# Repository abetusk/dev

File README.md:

[Dev Blog](http://mechaelephant.com/dev/)
===

Overview
---

See my [Dev Blog](http://mechaelephant.com/dev/).

Mostly notes for myself in a Blog-esque presentation.

Uses `mkdocs` to generate a list of Blog-like entries.
`orderedlist` is used for the theme.

Compilation
---

```bash
$ mkdocs build
$ mkdocs serve
```

Workflow
---

As a convention, each blog entry is stored in it's own Markdown file, with a timestamp at the end in the form:

```
###### YYYY-MM-DD
```

The compilation workflow is pretty clunky.  To test local, make sure the `base` variable in `mkdocs.yml` is set to `"/"`.
For production deployment, set the `base` variable to `"/dev"`.

Make sure to update a new entry in:

* `wiki/home.md`
* `wiki/Home.textile`
* `wiki/_Sidebar.textile`
* `dev_theme/base.html`
* `mkdocs.yml`

Probably only the `base.html`, `home.md` and `mkdocs.yml` are actually needed.  The others were a hold over from
when I was trying to get things working under GitHub's wiki.

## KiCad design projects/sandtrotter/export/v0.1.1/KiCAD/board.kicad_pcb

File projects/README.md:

Projects
===

###### 2021-01-25

Generative Music
---

### Status

Have a rudimentary song generator at [familiar-synths.js](https://github.com/abetusk/dev/blob/release/notes/src/familiar-synths.js).

The song still isn't quite to my liking as all tunes it generates still sound "same-y".

Gibber (alpha playground) is still having problems with some of the presets, so the preset/instrument library
that can be drawn on is pretty limited.

### todo

* figure out how to make some reasonable generative synths instead of relying on presets
* remove drums at end so they stop
* find instrument sound levels with each other so they play well with each other
* add extra effects (pads, background texture, more complex beats/rythms) to score to help flesh it out
* figure out why the songs sound so stale

| | |
|---|---|
| priority | low |

Sandtrotter
---

### Status

Boards is generated but unordered and the test is unassembled.

### todo

* test out with a nano/arduino with a CR2032 cell to see you can vibrate the motor
* order boards
* create software for it

| | |
|---|---|
| priority | medium |

Live Free, Live Forever
---

### Status

Jacket is assembled but the backing board needs to be paired down.

If there's some way to make the backing easier, this would be ideal.

* Put EVA foam used for floors as a backing plane for the LEDs
* Put EVA foam in both front corners as backing
  - left is for electronics, suitably shoved in there to try and shield it from
    use and offer some strain relief
  - right is for battery
  - might need to elongate the wire from battery to electronics

### todo

* Need to fit to see if the positioning, EVA foam pruning and corner backing
  is reasonable

| | |
|---|---|
| priority | high |

BLDC Driver
---

### Status

Boards are ordered but need to be soldered and tested

* Tested boards
* Big hangup was the 'sense' that needed to either be tied to ground or
  go through a 1ohm resistor
* Let the smoke out of one by connecting it to a large BLDC motor
* Ordered more motors

[src](https://meowcad.com/project?projectId=9ff614c5-18d6-4155-b22e-76b0fd457886)

### todo

* Test with encoder
* Create two motor system with arms to create something interesting
* rev version (?)
  - on board atmega
  - on board encoder (integrated)

| | |
|---|---|
| priority | high |

Seg16
---

### Status

Have a set of 10 boards (put on Tindie) but without a good
method for the diffusors.

The diffusors are laser cut from EVA foam but maybe they
would be better served by 3d printing them.
Seems like kind of a waste of material but who knows.

### todo

* create a clock out of them (or something) as a standalone project

| | |
|---|---|
| priority | medium |

Bloom3d
---

### Status

The 3d printing solution I was pursuing is not going to work.

I think a better method is to have cloth/Tyvek hinges sandwiched in between
laser cut/3d printed/whatever thin strips which then go to a central shaft.

Ordered some tiny stepper motors.
Hopefully they can be driven direct from an Arduino or, in the worst case,
driven by some small transistors.
With luck, I can connect the shaft directly to the platform.

### todo

* get tiny stepper to run (direct off an Arduino)
* construct test rig as proof of concept

| | |
|---|---|
| priority | high |

Frands
---

### Status

Still don't know how to approach this.

Some key points:

* Each layer does not have lights in between them, it's completely
  backlit by the back most panel, diffused from LEDs
* The spacing can be done with foam
* Put it in a frame

### todo

* figure out what the scene should be an implement it

| | |
|---|---|
| priority | low |

BTC Node
---

Create a full node with lightning support.

### Status

None.

### todo

* Either buy a pi + hdd or rent one that has enough space
* stand up node and play around with it

| | |
|---|---|
| priority | high |

Flitterhaus
---

### Status

Software is mostly created, though it needs to be tested a bit.

### todo

* run some outdoor tests on the solar + battery to discover feasibility

| | |
|---|---|
| priority | medium |

Music Similarity
---

### Status

Highly speculative, need to research more.

A modification to `sox` to allow for logarithm frequency spectrogram [here](http://jdesbonnet.blogspot.com/2014/02/sox-spectrogram-log-frequency-axis-and.html) ([gh](https://github.com/jdesbonnet/joe-desbonnet-blog/blob/master/projects/sox-log-spectrogram/spectrogram.c)).

### todo

* find a workflow to create spectrogram, output some type of constellation map
* go back from constellation map to sound to see what gets picked up

| | |
|---|---|
| priority | low |

OK Continuity
---

### Status

Initial investigation is good.
DeepSpeech is faster than real-time.

### todo

* test with usb microphone
* create interface (maybe with visual feedback)
* add some external trigger mechanisms

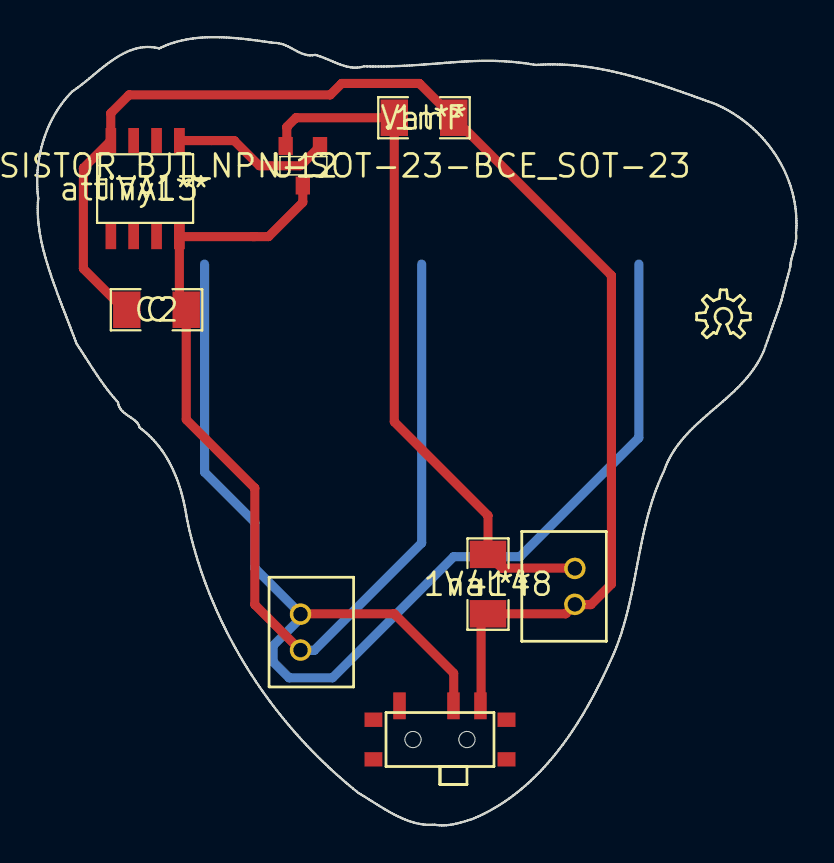
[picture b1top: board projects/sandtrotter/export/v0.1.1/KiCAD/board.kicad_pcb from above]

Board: 5 copper layers, 42.2 x 43.8 mm, 11 parts (0 on the bottom side), 5 nets.

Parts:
1n4148, .1mF: Val**; SM1206
C2: C; SM1206
U12: TRANSISTOR_BJT_NPN-SOT-23-BCE_SOT-23; SOT23
attiny13: VAL**; SO8E
bat: cr2032; BATT2032
ref: val; custom
ref**: val**; SLIDE_SWITCH_SMD
ref**#2: val**; OSHW-LOGO-S
ref**#3, ref**#4: val**; CON_JST_2PIN

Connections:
unnamed: 1n4148.2, .1mF.1, C2.1, attiny13.8, ref**.NC, ref**#4.1
unnamed: C2.2, U12.3, attiny13.4, bat.V-, ref**#3.2
unnamed: 1n4148.1, .1mF.2, U12.2, ref**#4.2
unnamed: U12.1, attiny13.5
unnamed: bat.V1, bat.V2, ref**.COM, ref**#3.1

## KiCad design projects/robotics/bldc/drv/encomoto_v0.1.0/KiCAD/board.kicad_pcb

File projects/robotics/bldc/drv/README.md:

GoPro Driver (L6234)
===

| | |
|---|---|
|  |  | 

BLDC driver based on the L6234 chip.

**Mostly untested**.

Notes
---

* [l6234 datasheet](https://raw.githubusercontent.com/abetusk/manuals/master/datasheets/LD6234.pdf)
* [NearZero](http://skysedge.us/robotics/nearzero/electrical/NearZeroSchematic.pdf)

Tying `SENSE1` and `SENSE2` to ground (or perhaps to a 1 ohm resistor to ground) is necessary,
as I found out.

License
---

CC0

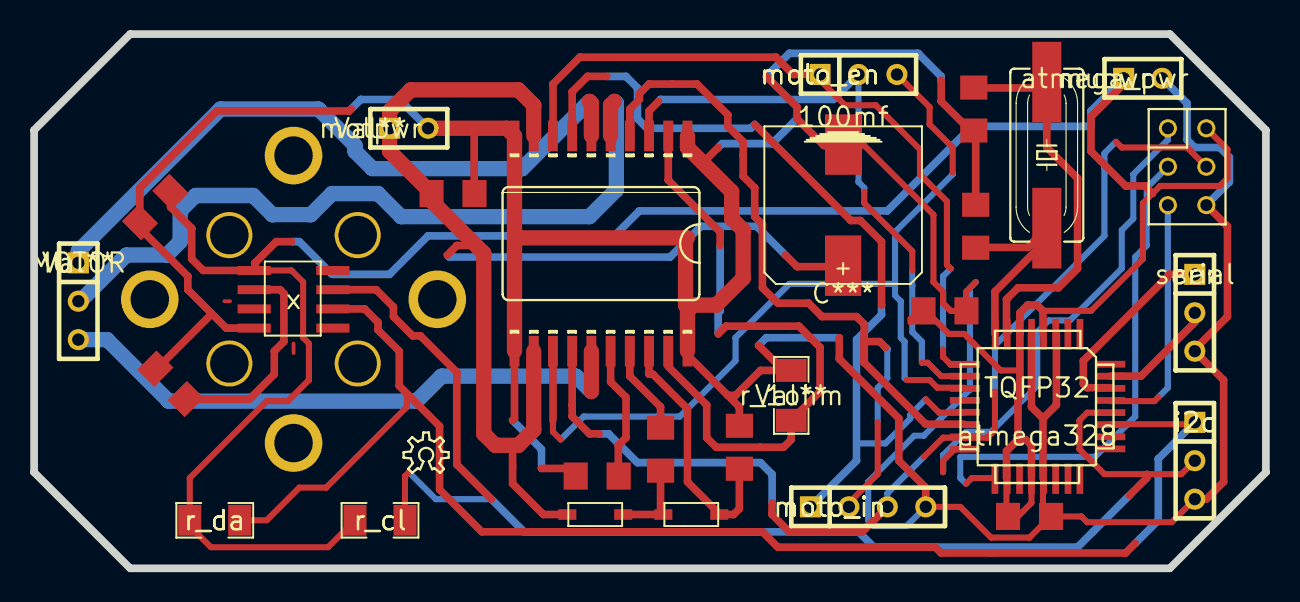
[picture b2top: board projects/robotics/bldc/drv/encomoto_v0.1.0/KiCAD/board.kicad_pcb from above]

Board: 5 copper layers, 81.4 x 35.3 mm, 30 parts (0 on the bottom side), 26 nets.

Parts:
100mf: C***; c_elec_10x10
>NAME: val**; M2X3
>NAME#2: >VALUE; HC49UP
C0e, C12: 100nF; C1206
C1e: 1uF; C1206
C1m: 1uf; C1206
C2: 10nf; C1206
C3: .22uf; C1206
C9: 4.7uF; C1206
C10, C11: 22pF; C1206
D0, D1: 1n4148; SOD-123
MOTOR: Val**; SIL-3
TQFP32: atmega328; TQFP32
U0: l6234; powerSO20
c0: .1uf; C1206
enc: as5600; SOIC-8
i2c: i2c; SIL-3
moto_en: moto_en; SIL-3
moto_in: moto_in; SIL-4
motpwr: Val**; SIL-2
mupwr: atmega_pwr; SIL-2
r_1ohm: Val**; SM1206
r_cl: r_cl; SM1206
r_da: r_da; SM1206
ref**: val**; OSHW-LOGO-S
ser: serial; SIL-3
x: meow_gopro_bot_screw

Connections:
GND: TQFP32.9, TQFP32.14, TQFP32.17, TQFP32.29, TQFP32.31
unnamed: TQFP32.11, TQFP32.12
unnamed: C1e.1, enc.2
unnamed: >NAME.2, C0e.1, C9.1, C12.1, TQFP32.18, enc.1, mupwr.1, r_cl.1, r_da.1
unnamed: enc.7, i2c.2, r_cl.2
unnamed: enc.6, i2c.1, r_da.2
unnamed: U0.2, U0.19, r_1ohm.1
unnamed: >NAME#2.2, C11.1
unnamed: >NAME#2.1, C10.1
unnamed: 100mf.2, >NAME.6, C0e.2, C1e.2, C1m.2, C3.2, C9.2, C10.2, C11.2, C12.2, U0.1, U0.10, U0.11, U0.20, c0.2, enc.4, i2c.3, moto_in.4, motpwr.2, mupwr.2, r_1ohm.2, ser.3
unnamed: U0.8, moto_en.1
unnamed: TQFP32.10, U0.3, moto_en.2
unnamed: U0.13, moto_en.3
unnamed: U0.7, moto_in.1
unnamed: U0.4, moto_in.2
unnamed: >NAME.1, TQFP32.16
unnamed: >NAME.4, TQFP32.15, U0.14, moto_in.3
unnamed: MOTOR.3, U0.15
unnamed: MOTOR.2, U0.5
unnamed: MOTOR.1, U0.6
unnamed: 100mf.1, D0.A, U0.9, U0.12, c0.1, motpwr.1
unnamed: C1m.1, U0.16
unnamed: C2.1, D0.C, D1.A
unnamed: C2.2, U0.17
unnamed: C3.1, D1.C, U0.18
VCC: TQFP32.3, TQFP32.4, TQFP32.13, TQFP32.26

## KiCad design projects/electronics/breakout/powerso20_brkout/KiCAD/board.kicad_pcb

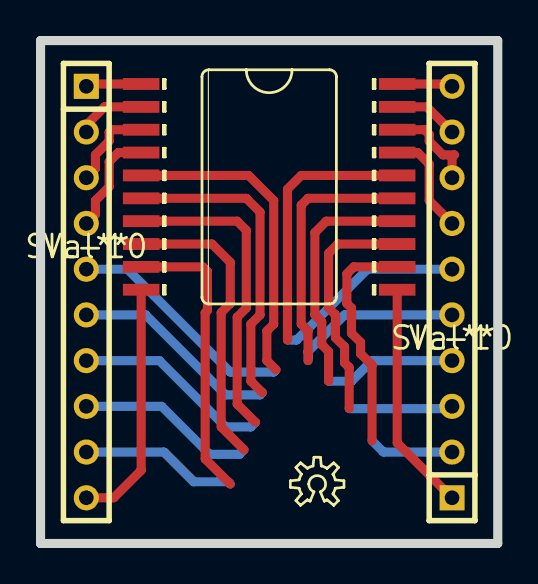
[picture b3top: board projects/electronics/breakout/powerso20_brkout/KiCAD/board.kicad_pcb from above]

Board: 5 copper layers, 25.4 x 27.9 mm, 4 parts (0 on the bottom side), 20 nets.

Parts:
>NAME: >VALUE; powerSO20
SIL-10, SIL-10#2: Val**; SIL-10
ref**: val**; OSHW-LOGO-S

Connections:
unnamed: >NAME.18, SIL-10.8
unnamed: >NAME.19, SIL-10.9
unnamed: >NAME.20, SIL-10.10
unnamed: >NAME.11, SIL-10.1
unnamed: >NAME.12, SIL-10.2
unnamed: >NAME.13, SIL-10.3
unnamed: >NAME.14, SIL-10.4
unnamed: >NAME.15, SIL-10.5
unnamed: >NAME.16, SIL-10.6
unnamed: >NAME.17, SIL-10.7
unnamed: >NAME.6, SIL-10#2.6
unnamed: >NAME.5, SIL-10#2.5
unnamed: >NAME.4, SIL-10#2.4
unnamed: >NAME.3, SIL-10#2.3
unnamed: >NAME.2, SIL-10#2.2
unnamed: >NAME.1, SIL-10#2.1
unnamed: >NAME.7, SIL-10#2.7
unnamed: >NAME.8, SIL-10#2.8
unnamed: >NAME.9, SIL-10#2.9
unnamed: >NAME.10, SIL-10#2.10

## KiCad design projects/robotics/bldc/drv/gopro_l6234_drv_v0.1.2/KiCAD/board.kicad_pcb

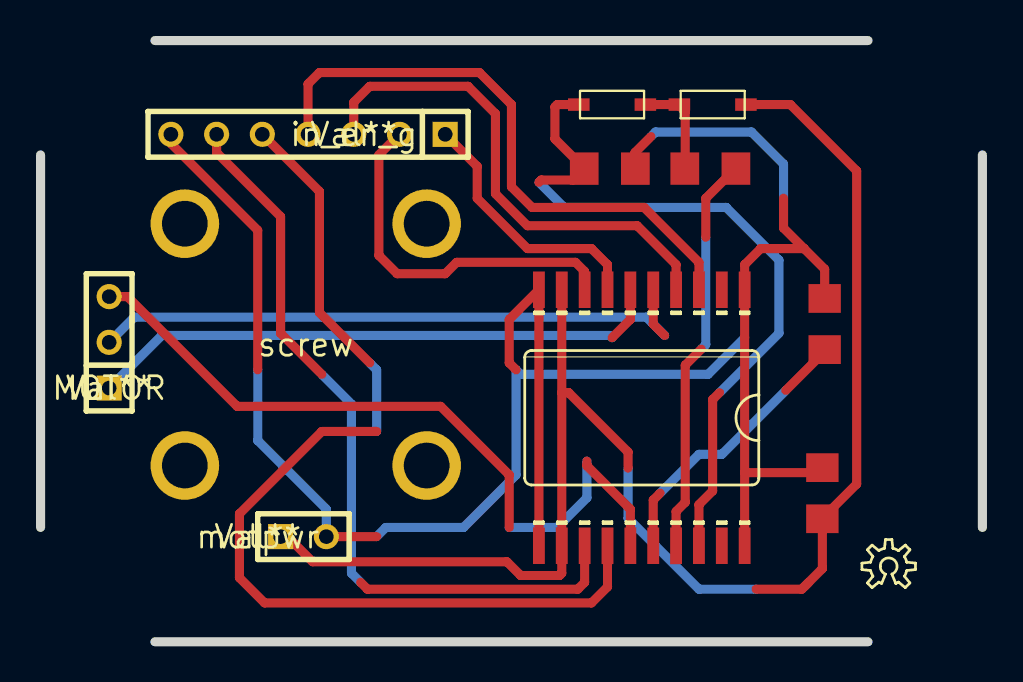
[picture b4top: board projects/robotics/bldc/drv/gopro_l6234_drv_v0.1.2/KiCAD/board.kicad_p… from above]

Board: 5 copper layers, 52.3 x 33.4 mm, 11 parts (0 on the bottom side), 15 nets.

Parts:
C1: 1uf; C1206
C2: 10nf; C1206
C3: .22uf; C1206
D0, D1: 1n4148; SOD-123
MOTOR: Val**; SIL-3
U0: l6234; powerSO20
c0: .1uf; C1206
in_en_g: Val**; SIL-7
motpwr: Val**; SIL-2
ref**: val**; OSHW-LOGO-S

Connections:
unnamed: C1.2, C3.2, U0.1, U0.10, U0.11, U0.20, c0.2, in_en_g.7, motpwr.2
unnamed: D0.A, U0.9, U0.12, c0.1, motpwr.1
unnamed: C1.1, U0.16
unnamed: C2.2, U0.17
unnamed: C3.1, D1.C, U0.18
unnamed: C2.1, D0.C, D1.A
unnamed: U0.3, in_en_g.4
unnamed: U0.7, in_en_g.1
unnamed: MOTOR.3, U0.15
unnamed: MOTOR.2, U0.5
unnamed: MOTOR.1, U0.6
unnamed: U0.8, in_en_g.2
unnamed: U0.4, in_en_g.3
unnamed: U0.14, in_en_g.5
unnamed: U0.13, in_en_g.6

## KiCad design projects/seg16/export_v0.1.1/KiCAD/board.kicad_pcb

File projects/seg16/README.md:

seg16
---

A 16 segment digit (base board) using WS2812B/SK6812 5050 parts.
Size should be about 5.2"x3.9" (132mmx100mm).

Currently this project is **semitested**.

Made with [MeowCAD](https://meowcad.com/project?projectId=4983569d-bf97-47ea-8737-0bbebbcf3797).

| | |
|---|---|
|  |  |

---

###### 2020-10-25

I ordered a set of 10 boards for about $50 from [JLCPCB](https://jlcpcb.com/),
or about $5 per assembled board, with shipping etc.
I used the Gerbers in `export/gerber` along with `BOM` and `CPL` files in the
`wd/jlcpcb` directory.

I haven't actually ordered 30 (which seems to be the max for JLCPCB?) but it comes
to about $112, or about $3.75 per assembled board, with shipping etc. ($86.28 + $25.41 shipping).

###### 2020-11-19

I haven't measured current consumption but [reports rate it](https://www.pjrc.com/how-much-current-do-ws2812-neopixel-leds-really-use/)
at anywhere from 30mA to 50mA (at 5V, so around .15W to .25W).
Each digit is 20 WS2812b, so at full bore that's anywhere from .60A to 1A (or .6W to 5W) per
digit.

If we call it 1A per digit, that means we need about a 20A (100W) power supply for a row of
20 digits.

From some simple experiments, it takes about 2-3 digits before there's a noticeable color degradation
in color.
So, for a single power supply in a row, it's probably wise to distribute power spaced every 2-3 digits.

###### 2020-11-19

The order of the LEDs is given by the following diagram:

License
---

Everything in this directory, unless explicitly denoted otherwise, is
under a CC0 license.

CC0

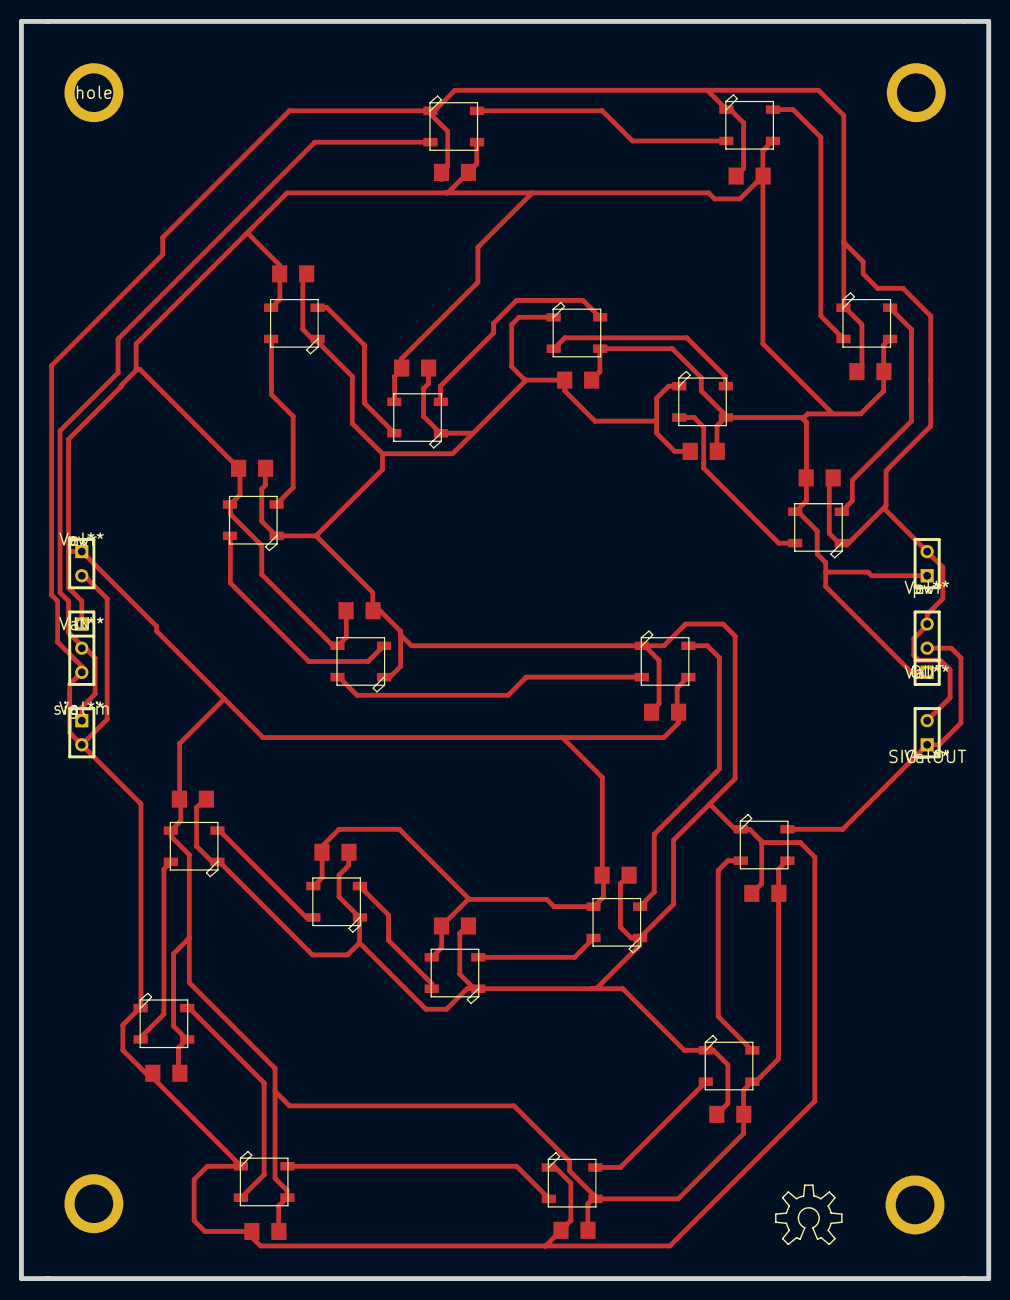
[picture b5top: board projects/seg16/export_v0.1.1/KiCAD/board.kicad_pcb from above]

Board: 5 copper layers, 101.7 x 132.2 mm, 48 parts (0 on the bottom side), 23 nets.

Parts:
C2, C3, C4, C5, C6, C7, C8, C9, C10, C11, C12, C13, C14, C15, C16, C17, C18, C19, C20: C; C1206
IN: Val**; SIL-3
OUT: Val**; SIL-3
SIG-OUT: Val**; SIL-2
U3, U6, U7, U8, U9, U10, U11, U12, U13, U14, U15, U16, U17, U18, U19, U20, U21, U22, U23: WS2812B; meowWS2812B
a0: WS2812B; meowWS2812B
aC0: 100nf; C1206
hole: meow_hole
pwr: Val**; SIL-2
pwr#2: Val**; SIL-2
ref**: val**; OSHW-LOGO-L
sig-in: Val**; SIL-2

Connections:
unnamed: OUT.2, SIG-OUT.1, U8.2-DOUT
unnamed: C2.2, C3.2, C4.2, C5.2, C6.2, C7.2, C8.2, C9.2, C10.2, C11.2, C12.2, C13.2, C14.2, C15.2, C16.2, C17.2, C18.2, C19.2, C20.2, IN.3, OUT.3, SIG-OUT.2, U3.3-GND, U6.3-GND, U7.3-GND, U8.3-GND, U9.3-GND, U10.3-GND, U11.3-GND, U12.3-GND, U13.3-GND, U14.3-GND, U15.3-GND, U16.3-GND, U17.3-GND, U18.3-GND, U19.3-GND, U20.3-GND, U21.3-GND, U22.3-GND, U23.3-GND, a0.3-GND, aC0.2, pwr.2, pwr#2.2, sig-in.2
unnamed: C2.1, C3.1, C4.1, C5.1, C6.1, C7.1, C8.1, C9.1, C10.1, C11.1, C12.1, C13.1, C14.1, C15.1, C16.1, C17.1, C18.1, C19.1, C20.1, IN.1, OUT.1, U3.1-VDD, U6.1-VDD, U7.1-VDD, U8.1-VDD, U9.1-VDD, U10.1-VDD, U11.1-VDD, U12.1-VDD, U13.1-VDD, U14.1-VDD, U15.1-VDD, U16.1-VDD, U17.1-VDD, U18.1-VDD, U19.1-VDD, U20.1-VDD, U21.1-VDD, U22.1-VDD, U23.1-VDD, a0.1-VDD, aC0.1, pwr.1, pwr#2.1
unnamed: U3.4-DIN, a0.2-DOUT
unnamed: IN.2, a0.4-DIN, sig-in.1
unnamed: U3.2-DOUT, U6.4-DIN
unnamed: U6.2-DOUT, U7.4-DIN
unnamed: U7.2-DOUT, U20.4-DIN
unnamed: U9.4-DIN, U10.2-DOUT
unnamed: U10.4-DIN, U11.2-DOUT
unnamed: U11.4-DIN, U12.2-DOUT
unnamed: U12.4-DIN, U13.2-DOUT
unnamed: U15.4-DIN, U18.2-DOUT
unnamed: U14.4-DIN, U15.2-DOUT
unnamed: U16.2-DOUT, U17.4-DIN
unnamed: U17.2-DOUT, U21.4-DIN
unnamed: U18.4-DIN, U19.2-DOUT
unnamed: U19.4-DIN, U20.2-DOUT
unnamed: U21.2-DOUT, U22.4-DIN
unnamed: U22.2-DOUT, U23.4-DIN
unnamed: U14.2-DOUT, U16.4-DIN
unnamed: U13.4-DIN, U23.2-DOUT
unnamed: U8.4-DIN, U9.2-DOUT

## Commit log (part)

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2020-03-18 spindle on fan line
2020-04-02 Non-Violent communication in a nutshell
2020-04-18 spelling
2020-04-18 spelling and todo for instructions
2020-04-18 images
2020-04-18 webui
2020-04-18 webui screens
2020-04-18 svg for compute housing
2020-04-18 housing pic
2020-05-24 graphic in lflf readme
2020-07-19 do away with all that stuff, simple z-axis screw connector
2020-08-10 grbl pinout
2020-08-10 updating notes
2020-08-14 link
2020-10-25 some more documentation
2020-10-25 imperial dimensions
2020-11-25 removed potentially non-free files, added free/libre files
2020-12-21 fighting with markdown
2021-02-18 added license (cc0)
2021-02-18 adding cc0 images
2021-02-18 adding license ingrediant facts
2021-10-26 fighting with newer version of mkdocs
2021-10-26 Bump pillow in /projects/maslowcnc/software/GroundControl-master
    Bumps [pillow](https://github.com/python-pillow/Pillow) from 5.2.0 to 8.3.2.
    - [Release notes](https://github.com/python-pillow/Pillow/releases)
    - [Changelog](https://github.com/python-pillow/Pillow/blob/main/CHANGES.rst)
    - [Commits](https://github.com/python-pillow/Pillow/compare/5.2.0...8.3.2)
    ---
    updated-dependencies:
2022-01-13 Bump pillow in /projects/maslowcnc/software/GroundControl-master
    Bumps [pillow](https://github.com/python-pillow/Pillow) from 5.2.0 to 9.0.0.
    - [Release notes](https://github.com/python-pillow/Pillow/releases)
    - [Changelog](https://github.com/python-pillow/Pillow/blob/main/CHANGES.rst)
    - [Commits](https://github.com/python-pillow/Pillow/compare/5.2.0...9.0.0)
    ---
    updated-dependencies:
2022-03-12 Bump pillow in /projects/maslowcnc/software/GroundControl-master
    Bumps [pillow](https://github.com/python-pillow/Pillow) from 5.2.0 to 9.0.1.
    - [Release notes](https://github.com/python-pillow/Pillow/releases)
    - [Changelog](https://github.com/python-pillow/Pillow/blob/main/CHANGES.rst)
    - [Commits](https://github.com/python-pillow/Pillow/compare/5.2.0...9.0.1)
    ---
    updated-dependencies:
2022-05-29 power polling
2022-09-02 fixing error
    * mu term in product should be back to i, not j
2022-09-08 fixing markdown aggresion for latex matrix expression
2022-11-13 git notes
2022-11-18 formatting
    mathjax (on GH) apparently doesn't like blank lines?
2022-11-18 fixes for latex rendering
    fighting with markdown to get the `*` to render in LaTEX
2022-11-18 0 gh, 1 me
    still fighting with GH vs LaTEX/MathJax.
    It looks like Markdown gets confused when the `*` or `_` symbol is used, especially when it has a partner on the same line. The makeshift solution is to put a `}` directly before the `_` and a space 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
2022-11-22 Bump pillow in /projects/maslowcnc/software/GroundControl-master
    Bumps [pillow](https://github.com/python-pillow/Pillow) from 5.2.0 to 9.3.0.
    - [Release notes](https://github.com/python-pillow/Pillow/releases)
    - [Changelog](https://github.com/python-pillow/Pillow/blob/main/CHANGES.rst)
    - [Commits](https://github.com/python-pillow/Pillow/compare/5.2.0...9.3.0)
    ---
    updated-dependencies:
2022-12-03 fixes
2022-12-17 my continuing fight with GH flavored MD and Latex...
2022-12-30 fighting with latex md
2022-12-30 damn your eyes markdown
2022-12-30 quell jumping sums and roducts
2023-01-03 oof, wrong inequality
    * fixed inequality, added inequality method
    * ...
2023-01-06 mkdocs needs extra '\\' for returns in latex lines?
2023-01-06 latex lines in '$$' multiline instead of single line
2023-01-06 forgot some '\\', fighting with markdown latex
2023-01-06 more fighting with latex markdown, extra '\\'
2023-03-19 incomplete notes
2023-05-22 Bump requests in /projects/maslowcnc/software/GroundControl-master
    Bumps [requests](https://github.com/psf/requests) from 2.13.0 to 2.31.0.
    - [Release notes](https://github.com/psf/requests/releases)
    - [Changelog](https://github.com/psf/requests/blob/main/HISTORY.md)
    - [Commits](https://github.com/psf/requests/compare/v2.13.0...v2.31.0)
    ---
    updated-dependencies:
2023-08-08 Update Belief-Propagation.md
    proper rendering of function `g()` in latex
2023-08-11 Update Belief-Propagation.md
    images don't work in tables now?
    wrapped the image in a paragraph with equation
2023-10-03 Bump pillow in /projects/maslowcnc/software/GroundControl-master
    Bumps [pillow](https://github.com/python-pillow/Pillow) from 5.2.0 to 10.0.1.
    - [Release notes](https://github.com/python-pillow/Pillow/releases)
    - [Changelog](https://github.com/python-pillow/Pillow/blob/main/CHANGES.rst)
    - [Commits](https://github.com/python-pillow/Pillow/compare/5.2.0...10.0.1)
    ---
    updated-dependencies:
2023-11-12 Update Statistical-Mechanics-For-Computer-Scientists.md
    latex formatting gets confused inside parentheses. Add space after parenthesis to fix.
    This fails:
    ```
    ($\lg(\cdot)$)
    ```
    This works:
2024-01-12 Update Distance-Metrics.md
    fighting with gh flavored mathjax
    sum needs to be enclosed in curlies to come out right
2024-02-09 Update 2D-Random-Walk-Range.md
    ...my eternal war with gh md and latex formatting
2024-02-09 Update 2D-Random-Walk-Range.md
    curly bracket extra backslash escape
2024-02-14 Update AVL-Tree.md
    table fix
2026-03-25 bump requests in /projects/maslowcnc/software/GroundControl-master
    Bumps [requests](https://github.com/psf/requests) from 2.13.0 to 2.33.0.
    - [Release notes](https://github.com/psf/requests/releases)
    - [Changelog](https://github.com/psf/requests/blob/main/HISTORY.md)
    - [Commits](https://github.com/psf/requests/compare/v2.13.0...v2.33.0)
    ---
    updated-dependencies:
2026-05-05 Bump pillow in /projects/maslowcnc/software/GroundControl-master
    Bumps [pillow](https://github.com/python-pillow/Pillow) from 5.2.0 to 12.2.0.
    - [Release notes](https://github.com/python-pillow/Pillow/releases)
    - [Changelog](https://github.com/python-pillow/Pillow/blob/main/CHANGES.rst)
    - [Commits](https://github.com/python-pillow/Pillow/compare/5.2.0...12.2.0)
    ---
    updated-dependencies:
